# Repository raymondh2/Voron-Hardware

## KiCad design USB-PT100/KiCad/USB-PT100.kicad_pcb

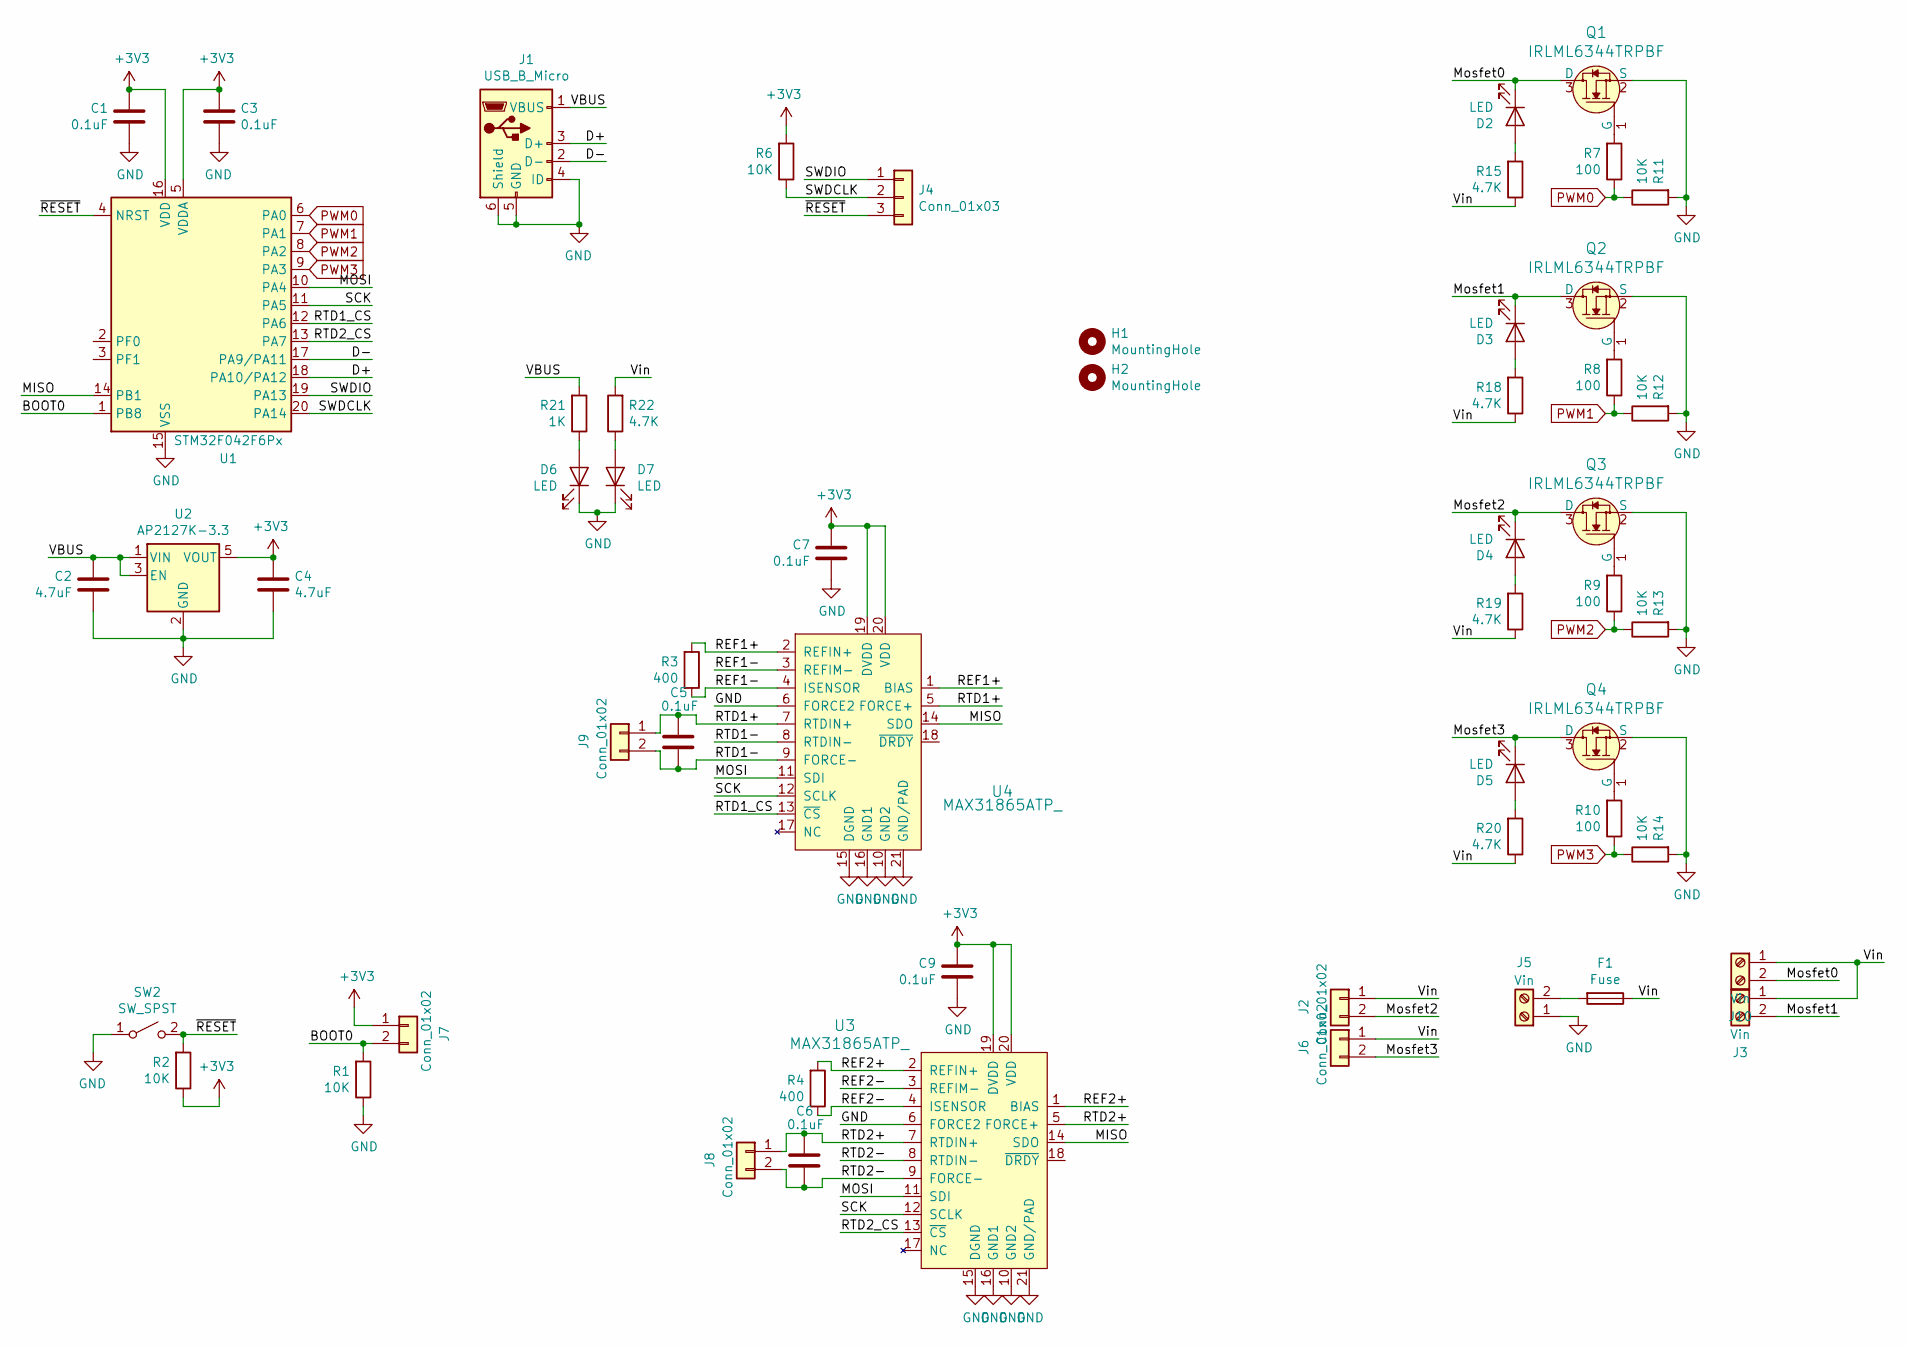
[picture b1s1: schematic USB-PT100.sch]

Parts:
C1, C3, C5, C6, C7, C9: 0.1uF; C_0805_2012Metric; MPN CC0805KRX7R9BB104; LCSC C49678
C2, C4: 4.7uF; C_0805_2012Metric; MPN CC0805KKX5R8BB475; LCSC C1779
D2, D3, D4, D5, D6, D7: LED; LED_0805_2012Metric; MPN 17-215SURC/S530-A2/TR8; LCSC C84256
F1: Fuse; 3544-2_FuseHolder
H1, H2: MountingHole; MountingHole_3.2mm_M3
J1: USB_B_Micro; Molex-105017-0001-USBMicroB; MPN 1050170001
J2, J6, J8, J9: Conn_01x02; JST_XH_B02B-XH-A_1x02_P2.50mm_Vertical
J3, J5, J10: Vin; 1x02_ScrewTerminal_Phoenix
J4: Conn_01x03; PinHeader_1x03_P2.54mm_Vertical
J7: Conn_01x02; PinHeader_1x02_P2.54mm_Vertical
Q1, Q2, Q3, Q4: IRLML6344TRPBF; SOT-23; MPN IRLML6344TRPBF; Digi-Key_PN IRLML6344TRPBFCT-ND
R1, R2, R6, R11, R12, R13, R14: 10K; R_0805_2012Metric; MPN RC0805JR-0710KL; LCSC C17414
R3, R4: 400; R_0805_2012Metric; MPN RC0805JR-0710KL; LCSC C17414
R7, R8, R9, R10: 100; R_0805_2012Metric; MPN RC0805JR-07100RL; LCSC C17408
R15, R18, R19, R20, R22: 4.7K; R_0805_2012Metric; MPN RC0805JR-074K7L; LCSC C17673
R21: 1K; R_0805_2012Metric; MPN RC0805JR-071KL; LCSC C17513
SW2: SW_SPST; 2PinTactileButton
U1: STM32F042F6Px; TSSOP-20_4.4x6.5mm_P0.65mm; MPN STM32F042F6P6; LCSC C81000
U2: AP2127K-3.3; SOT-23-5; MPN AP2127K-3.3TRG1; LCSC C156285
U3, U4: MAX31865ATP_; TQFN-20-1EP_5x5mm; MPN MAX31865ATP+; Digi-Key_PN MAX31865ATP+-ND

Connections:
+3V3: C1.2, C3.2, C4.2, C7.2, C9.2, J7.1, R2.1, R6.2, U1.5 (VDDA), U1.16 (VDD), U2.5 (VOUT), U3.19 (DVDD), U3.20 (VDD), U4.19 (DVDD), U4.20 (VDD)
/BOOT0: J7.2, R1.2, U1.1 (PB8)
/D+: J1.3 (D+), U1.18 (PA10/PA12)
/D-: J1.2 (D-), U1.17 (PA9/PA11)
/MISO: U1.14 (PB1), U3.14 (SDO), U4.14 (SDO)
/MOSI: U1.10 (PA4), U3.11 (SDI), U4.11 (SDI)
/Mosfet0: D2.1 (K), J10.2, Q1.3 (D)
/Mosfet1: D3.1 (K), J3.2, Q2.3 (D)
/Mosfet2: D4.1 (K), J2.2, Q3.3 (D)
/Mosfet3: D5.1 (K), J6.2, Q4.3 (D)
/REF1+: R3.2, U4.1 (BIAS), U4.2 (REFIN+)
/REF1-: R3.1, U4.3 (REFIM-), U4.4 (ISENSOR)
/REF2+: R4.2, U3.1 (BIAS), U3.2 (REFIN+)
/REF2-: R4.1, U3.3 (REFIM-), U3.4 (ISENSOR)
/RTD1+: C5.1, J9.1, U4.5 (FORCE+), U4.7 (RTDIN+)
/RTD1-: C5.2, J9.2, U4.8 (RTDIN-), U4.9 (FORCE-)
/RTD1_CS: U1.12 (PA6), U4.13 (~CS)
/RTD2+: C6.1, J8.1, U3.5 (FORCE+), U3.7 (RTDIN+)
/RTD2-: C6.2, J8.2, U3.8 (RTDIN-), U3.9 (FORCE-)
/RTD2_CS: U1.13 (PA7), U3.13 (~CS)
/SCK: U1.11 (PA5), U3.12 (SCLK), U4.12 (SCLK)
/SWDCLK: J4.2, R6.1, U1.20 (PA14)
/SWDIO: J4.1, U1.19 (PA13)
/VBUS: C2.2, J1.1 (VBUS), R21.2, U2.1 (VIN), U2.3 (EN)
/Vin: F1.1, J2.1, J3.1, J6.1, J10.1, R15.1, R18.1, R19.1, R20.1, R22.2
/~RESET: J4.3, R2.2, SW2.2 (B), U1.4 (NRST)
GND: C1.1, C2.1, C3.1, C4.1, C7.1, C9.1, D6.1 (K), D7.1 (K), J1.4 (ID), J1.5 (GND), J1.6 (Shield), J5.1, Q1.2 (S), Q2.2 (S), Q3.2 (S), Q4.2 (S), R1.1, R11.2, R12.2, R13.2, R14.2, SW2.1 (A), U1.15 (VSS), U2.2 (GND), U3.6 (FORCE2), U3.10 (GND2), U3.15 (DGND), U3.16 (GND1), U3.21 (GND/PAD), U4.6 (FORCE2), U4.10 (GND2), U4.15 (DGND), U4.16 (GND1), U4.21 (GND/PAD)
unnamed: D2.2 (A), R15.2
unnamed: D3.2 (A), R18.2
unnamed: D4.2 (A), R19.2
unnamed: D5.2 (A), R20.2
unnamed: D6.2 (A), R21.1
unnamed: D7.2 (A), R22.1
unnamed: F1.2, J5.2
unnamed: Q1.1 (G), R7.2
unnamed: Q2.1 (G), R8.2
unnamed: Q3.1 (G), R9.2
unnamed: Q4.1 (G), R10.2
PWM0: R7.1, R11.1, U1.6 (PA0)
PWM1: R8.1, R12.1, U1.7 (PA1)
PWM2: R9.1, R13.1, U1.8 (PA2)
PWM3: R10.1, R14.1, U1.9 (PA3)

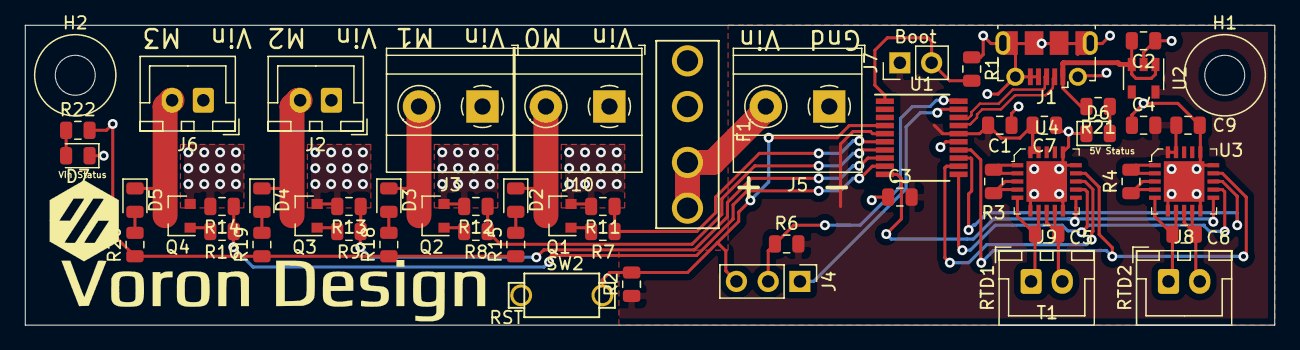
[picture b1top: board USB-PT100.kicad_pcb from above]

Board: 2 copper layers, 100.0 x 24.0 mm, 55 parts (0 on the bottom side), 42 nets.

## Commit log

2021-03-17 Add pt100usb
